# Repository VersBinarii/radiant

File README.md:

# Radiant
Touch screen controlled light dimmer

# What is it
The dimming of light bulb it triggered by a touch screen.
It's a Leading-Edge dimmer so it should work even with modern led light bulbs that
are not dimmable in practice

# Schematics
Check the schematics folder for the Ki-Cad schematics and board design

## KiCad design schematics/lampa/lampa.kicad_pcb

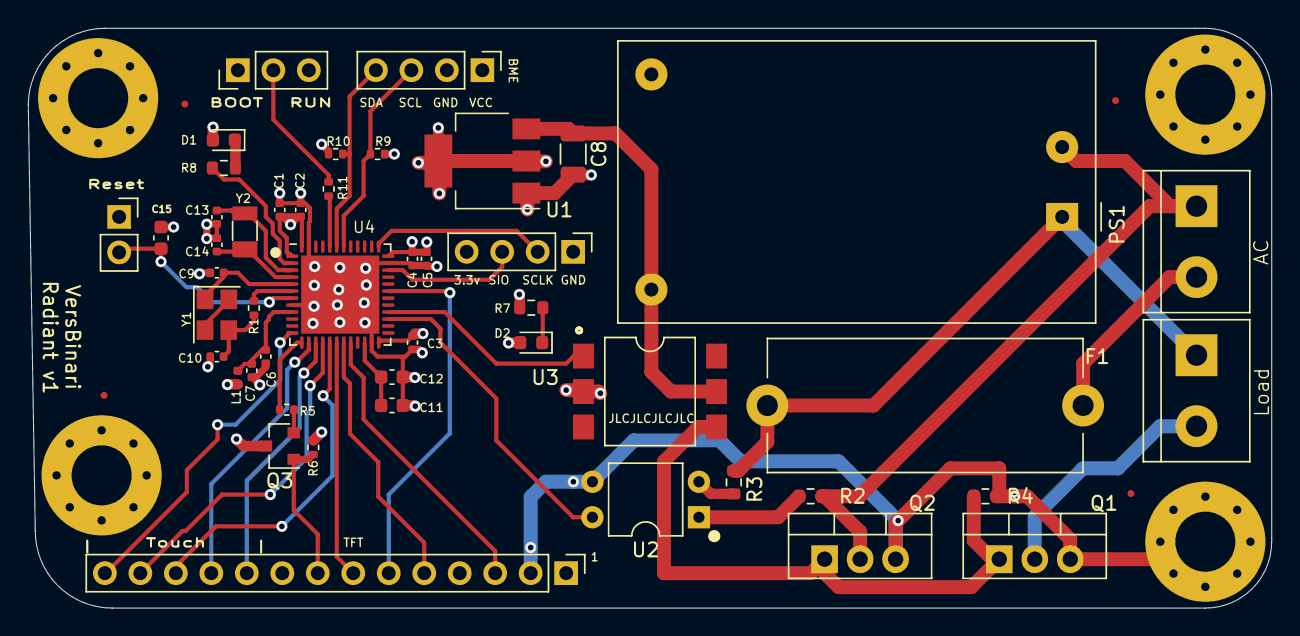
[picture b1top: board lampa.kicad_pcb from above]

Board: 4 copper layers, 89.0 x 41.5 mm, 51 parts (0 on the bottom side), 42 nets.

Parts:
C1: 4.7uF; C_0402_1005Metric
C2, C3, C4, C5: 100nF; C_0402_1005Metric
C6: 1uF; C_0402_1005Metric
C7: 10nF; C_0402_1005Metric
C8: 10uF; C_1206_3216Metric
C9, C10, C13, C14: 20pF; C_0402_1005Metric
C11, C12: 2.2uF; C_0603_1608Metric
C15: 100nF; C_0603_1608Metric
D1: LED BLUE; LED_0603_1608Metric
D2: LED GREEN; LED_0603_1608Metric
F1: Fuse; Fuseholder_Cylinder-5x20mm_Stelvio-Kontek_PTF78_Horizontal_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
H1, H2, H3, H4: MountingHole_Pad; MountingHole_4.3mm_M4_Pad_Via
J1, J2: Screw_Terminal_01x02; TerminalBlock_bornier-2_P5.08mm
J3: Conn_01x14; PinHeader_1x14_P2.54mm_Vertical
J4, J5: Conn_01x04; PinHeader_1x04_P2.54mm_Vertical
L1: 39nH; L_0402_1005Metric
PS1: HLK-PM12; Converter_ACDC_HiLink_HLK-PMxx
Q1, Q2: IRF740; TO-220-3_Vertical
Q3: S8050; SOT-23
R1: 47; R_0402_1005Metric
R2, R3: 47K; R_0603_1608Metric
R4: 10K; R_0603_1608Metric
R5: 22K; R_0402_1005Metric
R6: 2K; R_0402_1005Metric
R7, R8: 680; R_0603_1608Metric
R9, R10: 4.7K; R_0402_1005Metric
R11: 10K; R_0402_1005Metric
SW1: SW_SPST; PinSocket_1x02_P2.54mm_Vertical
SW2: SW_SPDT; PinHeader_1x03_P2.54mm_Vertical
U1: AMS1117-3.3; SOT-223-3_TabPin2
U2: LTV-814; DIP-4_W7.62mm
U3: 4N35; SMDIP-6_W9.53mm_Clearance8mm
U4: STM32F411CEUx; QFN-48-1EP_7x7mm_P0.5mm_EP5.6x5.6mm
Y1: 16MHz; Crystal_SMD_3225-4Pin_3.2x2.5mm
Y2: Crystal; Crystal_SMD_3215-2Pin_3.2x1.5mm

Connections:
+3.3VA: C6.1, C7.1, L1.2, U4.9
+3V3: C1.1, C2.1, C3.1, C4.1, C5.1, D1.2, D2.2, J3.1, J3.4, J4.4, J5.1, L1.1, Q3.3, R9.1, R10.1, SW2.1, U1.2, U4.1, U4.24, U4.36, U4.48
+12V: C8.1, PS1.3, U1.3, U3.5
BACKLIGHT_PWM: R5.2, U4.13
BLUE_LED: R8.1, U4.2
BME_SCL: J5.3, R9.2, U4.42
BME_SDA: J5.4, R10.2, U4.43
BOOT: R11.2, U4.44
GND: C1.2, C2.2, C3.2, C4.2, C5.2, C6.2, C7.2, C8.2, C9.2, C10.2, C11.2, C12.2, C13.2, C14.2, C15.2, H1.1, H2.1, H3.1, H4.1, J3.2, J4.1, J5.2, PS1.4, Q1.3, Q2.3, R4.2, R6.1, R7.1, SW1.1, SW2.3, U1.1, U2.3, U3.2, U4.8, U4.23, U4.35, U4.47, U4.49
HSE_IN: C9.1, U4.5, Y1.1
HSE_OUT: R1.1, U4.6
LCD_CLK: J3.7, U4.18
LCD_CS: J3.3, U4.20
LCD_DC: J3.5, U4.19
LCD_MOSI: J3.6, U4.31
LSE_IN: C13.1, U4.3, Y2.1
LSE_OUT: C14.1, U4.4, Y2.2
NRST: C15.1, SW1.2, U4.7
unnamed: C10.1, R1.2, Y1.3
unnamed: C11.1, C12.1, U4.22
unnamed: D1.1, R8.2
unnamed: D2.1, R7.2
unnamed: F1.1, J1.2
unnamed: F1.2, J2.1, PS1.1, R3.1
unnamed: J1.1, PS1.2, Q2.2, R2.1
unnamed: J2.2, Q1.2
unnamed: J3.8, Q3.1, R6.2
unnamed: Q1.1, Q2.1, R4.1, U3.4
unnamed: Q3.2, R5.1
unnamed: R2.2, U2.1
unnamed: R3.2, U2.2
unnamed: R11.1, SW2.2
unnamed: Y1.2, Y1.4
SWCLK: J4.2, U4.37
SWDIO: J4.3, U4.34
TOUCH_CLK: J3.10, U4.15
TOUCH_CS: J3.11, U4.14
TOUCH_IRQ: J3.14, U4.12
TOUCH_MISO: J3.13, U4.16
TOUCH_MOSI: J3.12, U4.17
TRIAK_CTRL: U3.1, U4.28
ZERO_CROSS_DETECT: U2.4, U4.27

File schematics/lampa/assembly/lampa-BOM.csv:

Comment,Designator,Footprint,LCSC
"4.7uF","C1","Capacitor_SMD:C_0402_1005Metric","C23733"
"20pF","C9,C10,C13,C14","Capacitor_SMD:C_0402_1005Metric","C1554"
"2.2uF","C11,C12","Capacitor_SMD:C_0603_1608Metric","C23630"
"100nF","C15","Capacitor_SMD:C_0603_1608Metric","C14663"
"100nF","C2,C3,C4,C5","Capacitor_SMD:C_0402_1005Metric","C1525"
"1uF","C6","Capacitor_SMD:C_0402_1005Metric","C52923"
"10nF","C7","Capacitor_SMD:C_0402_1005Metric","C15195"
"10uF","C8","Capacitor_SMD:C_1206_3216Metric","C13585"
"LED BLUE","D1","LED_SMD:LED_0603_1608Metric","C72041"
"LED GREEN","D2","LED_SMD:LED_0603_1608Metric","C72043"
"Fuse","F1","Fuse:Fuseholder_Cylinder-5x20mm_Stelvio-Kontek_PTF78_Horizontal_Open",""
"MountingHole_Pad","H1,H2,H3,H4","MountingHole:MountingHole_4.3mm_M4_Pad_Via",""
"Screw_Terminal_01x02","J1,J2","TerminalBlock:TerminalBlock_bornier-2_P5.08mm",""
"Conn_01x14","J3","Connector_PinHeader_2.54mm:PinHeader_1x14_P2.54mm_Vertical",""
"Conn_01x04","J4,J5","Connector_PinHeader_2.54mm:PinHeader_1x04_P2.54mm_Vertical",""
"39nH","L1","Inductor_SMD:L_0402_1005Metric","C26443"
"HLK-PM12","PS1","Converter_ACDC:Converter_ACDC_HiLink_HLK-PMxx",""
"IRF740","Q1,Q2","Package_TO_SOT_THT:TO-220-3_Vertical",""
"S8050","Q3","Package_TO_SOT_SMD:SOT-23","C2146"
"47","R1","Resistor_SMD:R_0402_1005Metric","C25118"
"4.7K","R9,R10","Resistor_SMD:R_0402_1005Metric",""
"10K","R11","Resistor_SMD:R_0402_1005Metric","C25744"
"47K","R2,R3","Resistor_SMD:R_0603_1608Metric","C25819"
"10K","R4","Resistor_SMD:R_0603_1608Metric","C25804"
"22K","R5","Resistor_SMD:R_0402_1005Metric","C25768"
"2K","R6","Resistor_SMD:R_0402_1005Metric","C4109"
"680","R7,R8","Resistor_SMD:R_0603_1608Metric","C23228"
"SW_SPST","SW1","Connector_PinSocket_2.54mm:PinSocket_1x02_P2.54mm_Vertical",""
"SW_SPDT","SW2","Connector_PinHeader_2.54mm:PinHeader_1x03_P2.54mm_Vertical",""
"AMS1117-3.3","U1","Package_TO_SOT_SMD:SOT-223-3_TabPin2","C6186"
"LTV-814","U2","Package_DIP:DIP-4_W7.62mm",""
"4N35","U3","Package_DIP:SMDIP-6_W9.53mm_Clearance8mm",""
"STM32F411CEUx","U4","Package_DFN_QFN:QFN-48-1EP_7x7mm_P0.5mm_EP5.6x5.6mm","C60420"
"16MHz","Y1","Crystal:Crystal_SMD_3225-4Pin_3.2x2.5mm","C9006"
"Crystal","Y2","Crystal:Crystal_SMD_3215-2Pin_3.2x1.5mm","C32346"

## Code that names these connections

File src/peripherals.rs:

use crate::dummy_pin::{DummyOutputPin, MyIrq};
use display_interface_spi::SPIInterface;
use ili9341::{DisplaySize240x320, Ili9341, Orientation};
use stm32f4xx_hal::{
    gpio::{Alternate, Edge, Input, NoPin, Output, Pin, PushPull},
    pac::{Peripherals, EXTI, SPI1, SPI5, TIM1},
    prelude::*,
    rcc::Clocks,
    spi::{Mode, NoMiso, Phase, Polarity, Spi},
    timer::{Channel, Delay},
};
use xpt2046::{self, Xpt2046};

/*
 * Touch driver interface
 * Controlled through the SPI 1 instance
 */
pub type TouchSpi = Spi<
    SPI1,
    (
        Pin<'A', 5, Alternate<5>>,
        Pin<'A', 6, Alternate<5>>,
        Pin<'A', 7, Alternate<5>>,
    ),
>;
pub type TouchDriver = Xpt2046<TouchSpi, Pin<'A', 4, Output<PushPull>>, MyIrq<'A', 2>>;

/*
 * LCD driver interface
 * Controlled through the SPI 5 instance
 */
pub type Lcd = Ili9341<
    SPIInterface<
        Spi<SPI5, (Pin<'B', 0, Alternate<6>>, NoPin, Pin<'A', 10, Alternate<6>>)>,
        Pin<'B', 1, Output>,
        Pin<'B', 2, Output>,
    >,
    DummyOutputPin,
>;

/*
 * Blue system led indicating system status
 */
pub type BlueLedPin = Pin<'C', 13, Output<PushPull>>;

/*
 *  Pin used for detection of the AC zeto crossing.
 *  Its connected to the LTV-814 opto coupler directly.
 *  Goes low whenever AC crosses the 0V.
 */
pub type ZeroCrossDetectPin = Pin<'B', 14, Input>;

/*
 * Used for driving the Triaks.
 * Connected directly to the 4N35 opto
 */
pub type TriakControlPin = Pin<'B', 15, Output<PushPull>>;

/*
 * TODO: Define error
 */
#[allow(clippy::type_complexity, clippy::result_unit_err)]
pub fn init_preipherals(
    mut dp: Peripherals,
) -> Result<
    (
        Clocks,
        BlueLedPin,
        ZeroCrossDetectPin,
        TriakControlPin,
        Lcd,
        TouchDriver,
        Delay<TIM1, 1000000>,
        EXTI,
    ),
    (),
> {
    let rcc = dp.RCC.constrain();
    let clocks = rcc.cfgr.use_hse(25.MHz()).sysclk(100.MHz()).freeze();

    let gpioa = dp.GPIOA.split();
    let gpiob = dp.GPIOB.split();
    let gpioc = dp.GPIOC.split();

    /*
     * We need a backlight control
     * TODO: We will need to be able to change the brighntess later
     */
    let backlight_pins = gpioa.pa3.into_alternate();
    let mut pwm = dp.TIM2.pwm_hz(backlight_pins, 10.kHz(), &clocks);
    pwm.enable(Channel::C4);
    pwm.set_duty(Channel::C4, pwm.get_max_duty() / 2);

    let blue_led = gpioc.pc13.into_push_pull_output();
    /*
     *  The ILI9341 driver
     */
    let lcd_clk = gpiob.pb0.into_alternate();
    let lcd_miso = NoMiso {};
    let lcd_mosi = gpioa.pa10.into_alternate().internal_pull_up(true);
    let lcd_dc = gpiob.pb1.into_push_pull_output();
    let lcd_cs = gpiob.pb2.into_push_pull_output();
    let mode = Mode {
        polarity: Polarity::IdleLow,
        phase: Phase::CaptureOnFirstTransition,
    };
    let lcd_spi = dp
        .SPI5
        .spi((lcd_clk, lcd_miso, lcd_mosi), mode, 8.MHz(), &clocks);
    let spi_iface = SPIInterface::new(lcd_spi, lcd_dc, lcd_cs);
    let dummy_reset = DummyOutputPin::default();
    let mut delay = dp.TIM1.delay_us(&clocks);
    let lcd = Ili9341::new(
        spi_iface,
        dummy_reset,
        &mut delay,
        Orientation::PortraitFlipped,
        DisplaySize240x320,
    )
    .unwrap();
    // Touch interface
    let mut touch_irq = gpioa.pa2.into_pull_up_input();
    let mut syscfg = dp.SYSCFG.constrain();
    touch_irq.make_interrupt_source(&mut syscfg);
    touch_irq.trigger_on_edge(&mut dp.EXTI, Edge::Falling);
    touch_irq.enable_interrupt(&mut dp.EXTI);
    let touch_cs = gpioa.pa4.into_push_pull_output();
    let touch_clk = gpioa.pa5.into_alternate();
    let touch_mosi = gpioa.pa7.into_alternate().internal_pull_up(true);
    let touch_miso = gpioa.pa6.into_alternate();
    let touch_spi = Spi::new(
        dp.SPI1,
        (touch_clk, touch_miso, touch_mosi),
        mode,
        4.MHz(),
        &clocks,
    );

    let xpt_drv = Xpt2046::new(
        touch_spi,
        touch_cs,
        MyIrq(touch_irq),
        xpt2046::Orientation::PortraitFlipped,
    );

    let mut zero_crossing = gpiob.pb14.into_pull_up_input();
    zero_crossing.make_interrupt_source(&mut syscfg);
    zero_crossing.trigger_on_edge(&mut dp.EXTI, Edge::Falling);
    zero_crossing.enable_interrupt(&mut dp.EXTI);
    let triak_ctrl = gpiob.pb15.into_push_pull_output();

    Ok((
        clocks,
        blue_led,
        zero_crossing,
        triak_ctrl,
        lcd,
        xpt_drv,
        delay,
        dp.EXTI,
    ))
}

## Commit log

2022-04-20 Working but requires calibration fix
2022-04-21 Got touch controller working
2022-08-25 Update dependencies
2022-08-25 Add xpt2046 local exti handler impl
2022-08-25 Lets press some buttons
2022-08-25 Basic gui interaction
2022-08-25 Add PCB scematics
2022-08-29 Use the ILI9341 with the e-h alpha 7 version
2022-08-29 Move the initialization to separate module
